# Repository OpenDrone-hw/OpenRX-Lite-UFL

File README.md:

# OpenRX Lite-UFL

Open-source 2.4 GHz ExpressLRS radio control receiver module with telemetry,
for any radio-controlled build: cars, boats, robots and aircraft. OpenRX Lite-UFL
combines an ESP32-C3 and SX1281 with a U.FL link-antenna connector in a
10.0 x 11.5 mm board.
It passes the received channels over serial (CRSF) on its RX and TX pads to a
controller, for example a flight controller or a vehicle or robot controller.

## Specifications

| | |
|---|---|
| Band | 2.4 GHz |
| Radio | SX1281 |
| Antenna | U.FL |
| Telemetry power | 13 dBm (20 mW) |
| Protocol | CRSF |
| MCU | ESP32-C3 |
| Input | 5 V pad |
| Firmware | ExpressLRS |
| Flashing | Betaflight passthrough or Wi-Fi |
| Dimensions | 10.0 x 11.5 mm |
| PCB | 6-layer, 1.0 mm |

Technical write-up, part list and layout constraints: [AGENTS.md](AGENTS.md).

## In the line

What pairs with what, and what is available:
[opendrone.be](https://opendrone.be).

## Contributing

See [CONTRIBUTING.md](CONTRIBUTING.md).

## License

Hardware licensed under [CERN-OHL-S-2.0](https://ohwr.org/cern_ohl_s_v2.txt),
see [LICENSE](LICENSE).

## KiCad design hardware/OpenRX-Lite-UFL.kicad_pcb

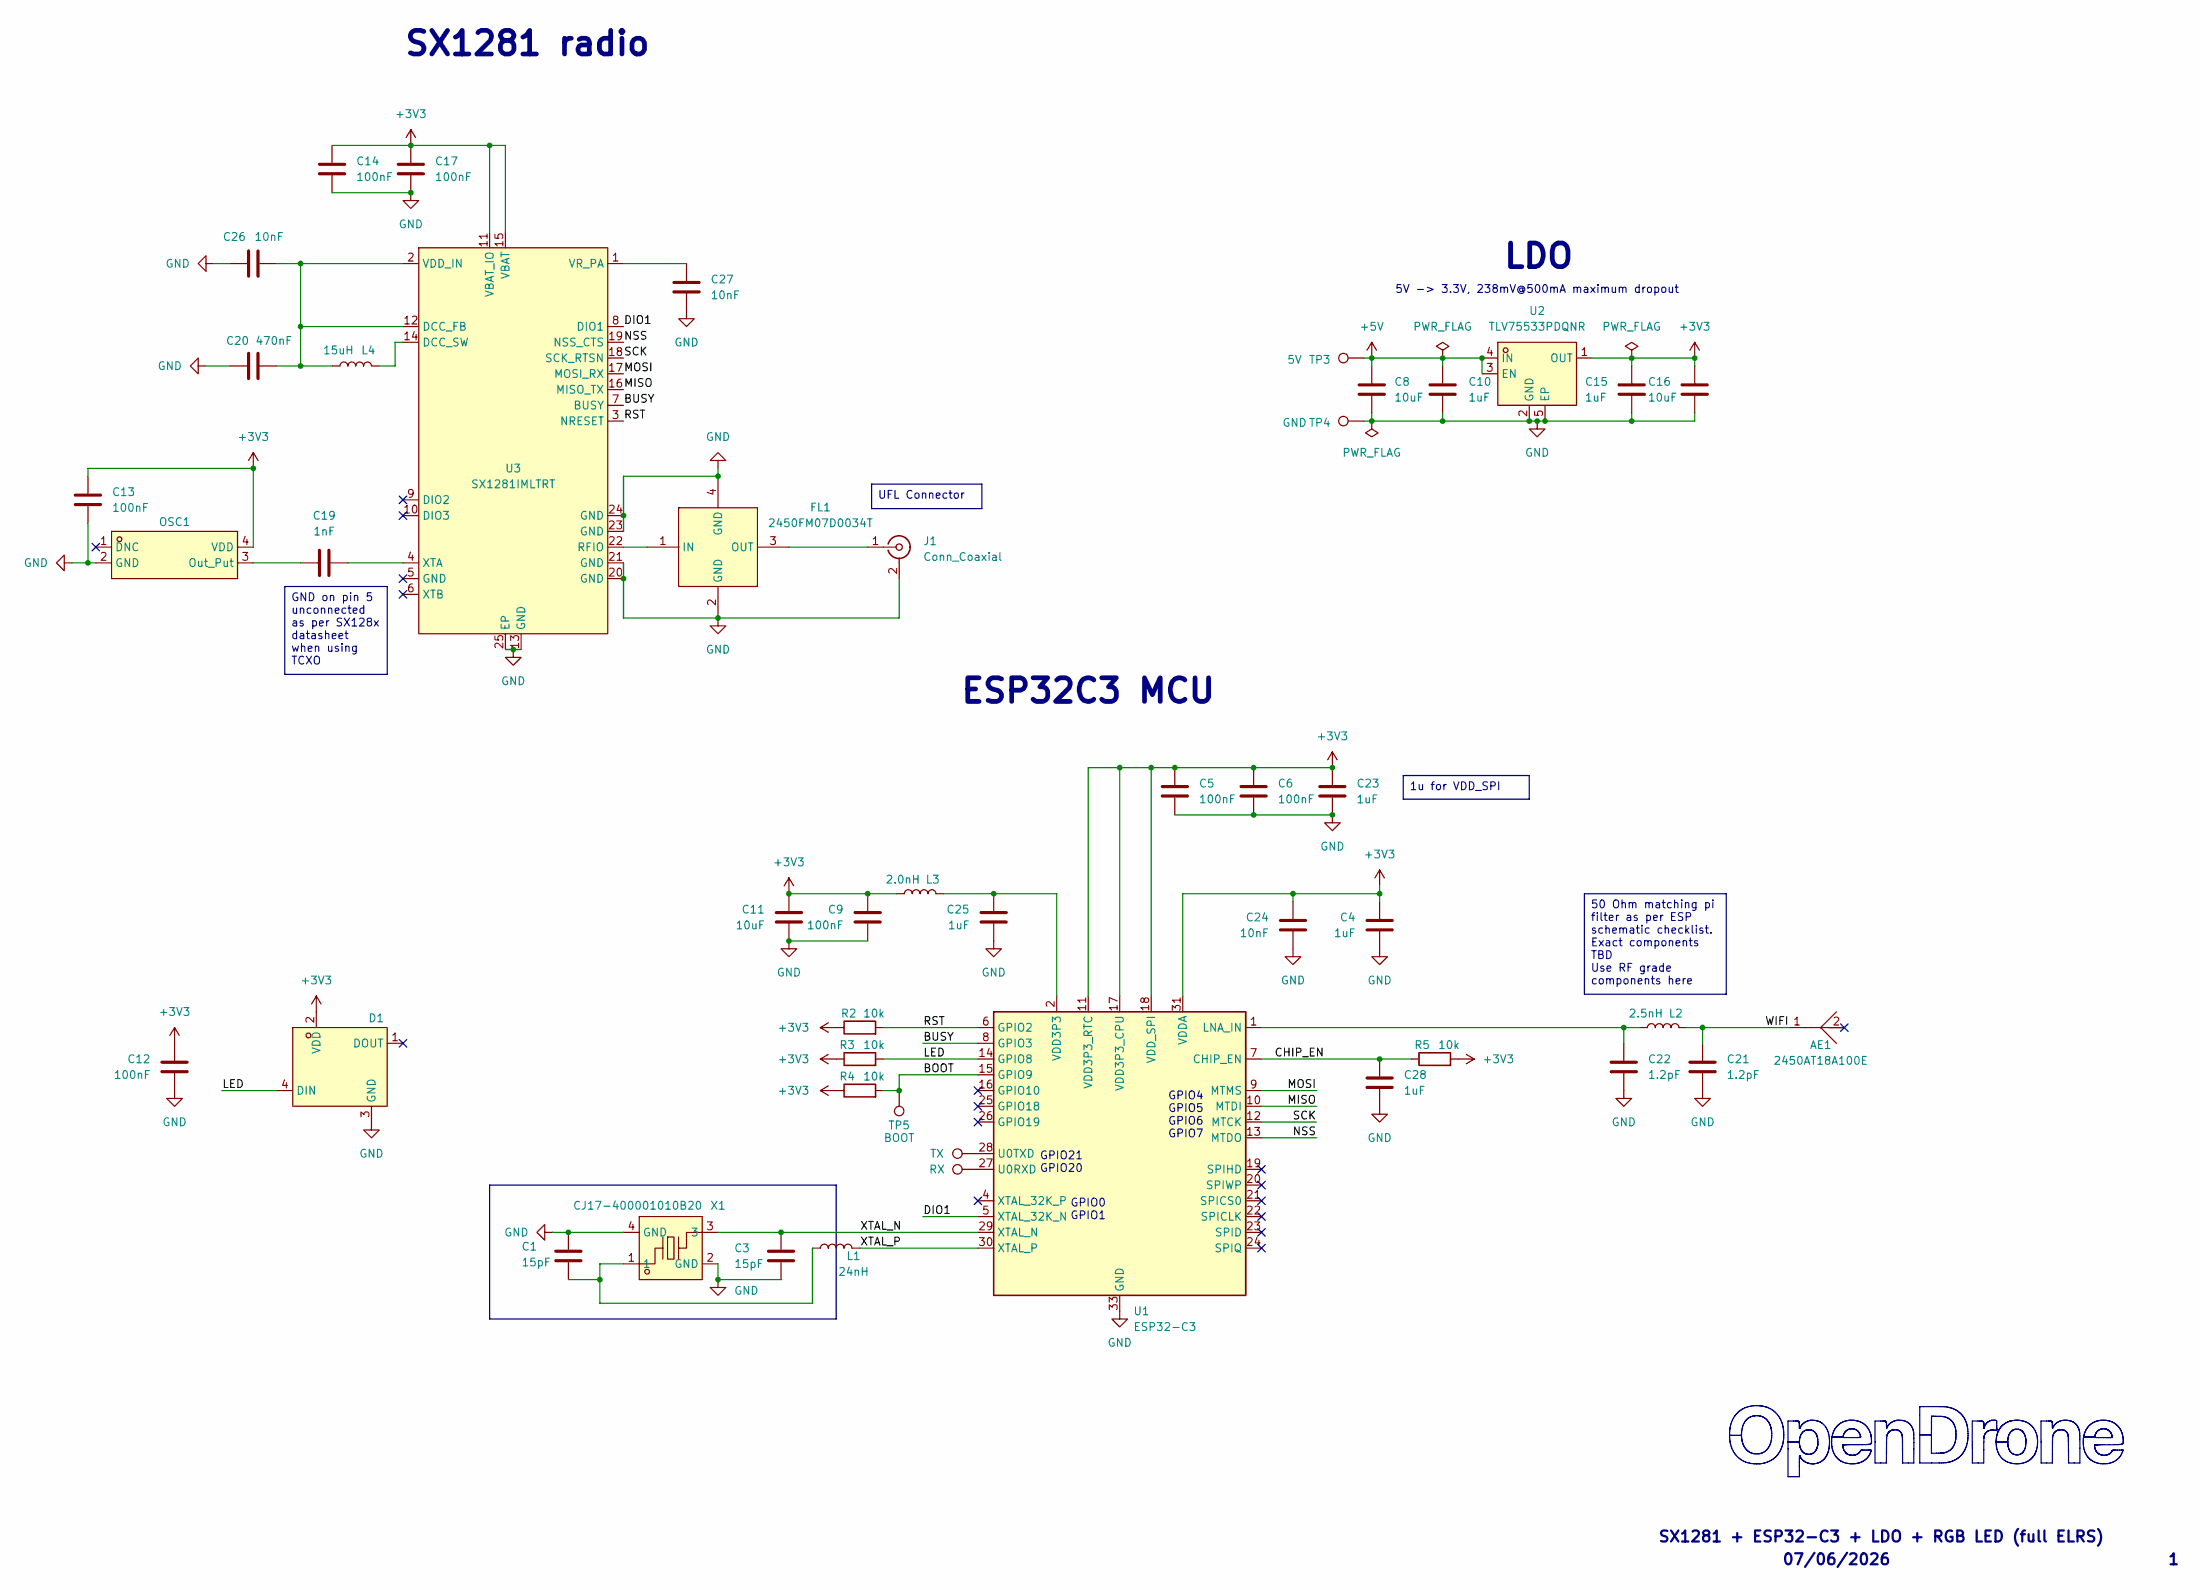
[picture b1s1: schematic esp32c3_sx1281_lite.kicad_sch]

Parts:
AE1: 2450AT18A100E; ANT-SMD_L3.2-W1.6; MPN 2450AT18A100E; LCSC Part C89334
C1, C3: 15pF; C_0201_0603Metric; MPN GRM0335C1H150JA01D; LCSC C85891
C4, C10, C15, C23, C25, C28: 1uF; C_0201_0603Metric; MPN GRM033R61A105ME44D; LCSC C76935
C5, C6, C9, C12, C13, C14, C17: 100nF; C_0201_0603Metric; MPN GRM033R61E104KE14D; LCSC C76939
C8, C16: 10uF; C_0402_1005Metric; MPN CL05A106MQ5NUNC; LCSC C15525
C11: 10uF; C_0402_1005Metric; MPN GRM155R60J106ME44D; LCSC C76991
C19: 1nF; C_0201_0603Metric; MPN 0201B102K500NT; LCSC C66942
C20: 470nF; C_0201_0603Metric; MPN GRM033R60J474KE90D; LCSC C85926
C21, C22: 1.2pF; C_0201_0603Metric; MPN GRM0335C1H1R2BA01D; LCSC C85895
C24, C26, C27: 10nF; C_0201_0603Metric; MPN GRM033R61A103KA01J; LCSC C2168164
D1: XL-1010RGBC-WS2812B; LED-SMD_4P-L1.0-W1.0-TL_XL-1010RGBC-WS2812B; MPN XL-1010RGBC-2812B; LCSC C5349953
FL1: 2450FM07D0034T; FILTER-SMD_4P-L1.0-W0.5-L; MPN 2450FM07D0034T; LCSC Part_1 C2651081
J1: Conn_Coaxial; U.FL_Hirose_U.FL-R-SMT-1_Vertical; MPN U.FL-R-SMT-1(80); LCSC C88374
L1: 24nH; L_0201_0603Metric; MPN LQP03TN24NH02D; LCSC C206441
L2: 2.5nH; L_0201_0603Metric; MPN LQP03TN2N5C02D; LCSC C206435
L3: 2.0nH; L_0201_0603Metric; MPN LQP03TN2N0B02D; LCSC C86125
L4: 15uH; L_0805_2012Metric; MPN MLZ2012M150WT000; LCSC C383402
OSC1: OW7EL89CENUNFAYLC-52M; OSC-SMD_4P-L2.0-W1.6-BL_TXC_7Z; MPN OW7EL89CENUNFAYLC-52M; LCSC Part C22434896
R2, R3, R4, R5: 10k; R_0201_0603Metric; MPN RC0201FR-0710KL; LCSC C106225
TP1: RX; SolderPad_1.2x2.0mm
TP2: TX; SolderPad_1.2x2.0mm
TP3: 5V; SolderPad_1.2x2.0mm
TP4: GND; SolderPad_1.2x2.0mm
TP5: BOOT; SolderPad_1.2x2.0mm
U1: ESP32-C3; QFN-32-1EP_5x5mm_P0.5mm_EP3.7x3.7mm; MPN ESP32-C3FH4; LCSC C2858491
U2: TLV75533PDQNR; X2SON-4_L1.0-W1.0-P0.65-TL-EP; MPN TLV75533PDQNR; LCSC Part C2861882
U3: SX1281IMLTRT; QFN-24_L4.0-W4.0-P0.50-TL-EP2.6; MPN SX1281IMLTRT; LCSC Part C2151551
X1: CJ17-400001010B20; CRYSTAL-SMD_4P-L1.6-W1.2-BL; MPN CJ17-400001010B20; LCSC Part C2875272

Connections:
+3V3: C4.1, C5.1, C6.1, C9.1, C11.1, C12.1, C13.1, C14.1, C15.1, C16.1, C17.1, C23.1, C24.1, D1.2 (VDD), L3.2, OSC1.4 (VDD), R2.1, R3.1, R4.1, R5.2, U1.11 (VDD3P3_RTC), U1.17 (VDD3P3_CPU), U1.18 (VDD_SPI), U1.31 (VDDA), U1.32 (VDDA), U2.1 (OUT), U3.11 (VBAT_IO), U3.15 (VBAT)
+5V: C8.1, C10.1, TP3.1 (1_1), U2.3 (EN), U2.4 (IN)
/ESP32-C3 + SX1281 Core (UFL)/BOOT: R4.2, TP5.1 (1_1), U1.15 (GPIO9)
/ESP32-C3 + SX1281 Core (UFL)/BUSY: U1.8 (GPIO3), U3.7 (BUSY)
/ESP32-C3 + SX1281 Core (UFL)/CHIP_EN: C28.1, R5.1, U1.7 (CHIP_EN)
/ESP32-C3 + SX1281 Core (UFL)/DIO1: U1.5 (XTAL_32K_N), U3.8 (DIO1)
/ESP32-C3 + SX1281 Core (UFL)/LED: D1.4 (DIN), R3.2, U1.14 (GPIO8)
/ESP32-C3 + SX1281 Core (UFL)/MISO: U1.10 (MTDI), U3.16 (MISO_TX)
/ESP32-C3 + SX1281 Core (UFL)/MOSI: U1.9 (MTMS), U3.17 (MOSI_RX)
/ESP32-C3 + SX1281 Core (UFL)/NSS: U1.13 (MTDO), U3.19 (NSS_CTS)
/ESP32-C3 + SX1281 Core (UFL)/RST: R2.2, U1.6 (GPIO2), U3.3 (NRESET)
/ESP32-C3 + SX1281 Core (UFL)/SCK: U1.12 (MTCK), U3.18 (SCK_RTSN)
/ESP32-C3 + SX1281 Core (UFL)/WIFI: AE1.1, C21.1, L2.1
/ESP32-C3 + SX1281 Core (UFL)/XTAL_N: C3.1, U1.29 (XTAL_N), X1.3
/ESP32-C3 + SX1281 Core (UFL)/XTAL_P: L1.2, U1.30 (XTAL_P)
GND: C1.2, C3.2, C4.2, C5.2, C6.2, C8.2, C9.2, C10.2, C11.2, C12.2, C13.2, C14.2, C15.2, C16.2, C17.2, C20.1, C21.2, C22.2, C23.2, C24.2, C25.2, C26.1, C27.2, C28.2, D1.3 (GND), FL1.2 (GND), FL1.4 (GND), J1.2 (Ext), OSC1.2 (GND), TP4.1 (1_1), U1.33 (GND), U2.2 (GND), U2.5 (EP), U3.13 (GND), U3.20 (GND), U3.21 (GND), U3.23 (GND), U3.24 (GND), U3.25 (EP), X1.2 (GND), X1.4 (GND)
unnamed: C1.1, L1.1, X1.1
unnamed: C25.1, L3.1, U1.2 (VDD3P3), U1.3 (VDD3P3)
unnamed: FL1.1 (IN), U3.22 (RFIO)
unnamed: FL1.3 (OUT), J1.1 (In)
unnamed: C19.1, OSC1.3 (Out_Put)
unnamed: C22.1, L2.2, U1.1 (LNA_IN)
unnamed: TP1.1 (1_1), U1.27 (U0RXD)
unnamed: TP2.1 (1_1), U1.28 (U0TXD)
unnamed: C20.2, C26.2, L4.1, U3.2 (VDD_IN), U3.12 (DCC_FB)
unnamed: L4.2, U3.14 (DCC_SW)
unnamed: C27.1, U3.1 (VR_PA)
unnamed: C19.2, U3.4 (XTA)

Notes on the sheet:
5V -> 3.3V, 238mV@500mA maximum dropout
GPIO0 GPIO1
GPIO21 GPIO20
SX1281 + ESP32-C3 + LDO + RGB LED (full ELRS)
GPIO4 GPIO5 GPIO6 GPIO7
SX1281 radio
LDO
ESP32C3 MCU
07/06/2026
GND on pin 5 unconnected as per SX128x datasheet when using TCXO
UFL Connector
1u for VDD_SPI
50 Ohm matching pi filter as per ESP schematic checklist. Exact components TBD Use RF grade components here

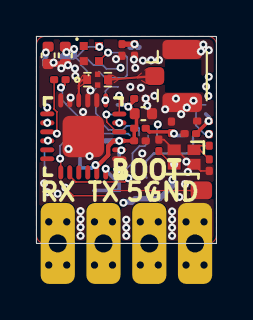
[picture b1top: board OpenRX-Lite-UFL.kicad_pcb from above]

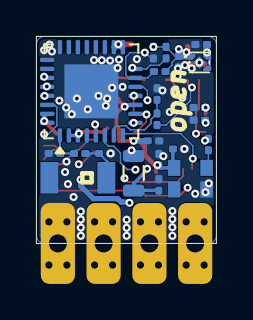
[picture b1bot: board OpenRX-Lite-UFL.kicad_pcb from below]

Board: 6 copper layers, 10.0 x 11.5 mm, 47 parts (22 on the bottom side), 28 nets.

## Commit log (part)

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2026-03-23 Fix Gemini crystal load caps to 18pF (C62164), matching Lite and Mono
2026-03-23 Repo cleanup: remove ERC reports, lock files, backup dirs, fix gitignore
2026-03-23 Add SolderPad_1.2x2.0mm with 25% rounded corners, 2.0mm pitch standard
2026-03-23 Import SKY13588-460LF SP3T RF switch (C2151906) into shared library
2026-03-23 Final topology: Mono + Gemini netlist with SKY13588 RF switch
    - SKY13588-460LF imported into shared library
    - Complete netlist for Mono (1×LR1121 + SKY13588 + Johanson IPD + DEA LPF → 1 UFL)
    - Gemini = 2× Mono RF chains + ESP32-C3 True Diversity GPIO mapping
    - GPIO maps match official ELRS Generic C3 LR1121 and True Diversity targets
    - Routing notes for RF paths included
    - Mono needs complete GPIO rewire to match ELRS target
2026-03-23 FINAL_NETLIST v3: SKY13588 as band combiner, RFX2401C kept for 100mW
    Based on RadioMaster XR4 teardown analysis:
    - SKY13588 serves as both sub-GHz path switch AND band combiner
    - Johanson IPD in direct-tie mode (RX/TX_LP/TX_HP joined) → SKY13588 J1
    - 2.4GHz: RFIO_HF → DEA LPF → RFX2401C → SKY13588 J2
    - SKY13588 RFC → DC block → UFL → dual-band antenna
    - RFX2401C kept for 100mW market parity
2026-03-24 Repo cleanup: final state for handoff
    - Clean README with architecture, BOM, CE notes, status
    - Remove dated analysis files (absorbed into FINAL_NETLIST + KICAD_WORKFLOW)
    - Remove stale OpenRX-Dual (archived), ERC reports, backups, prl files
    - Updated .gitignore for .kicad_dru, production backups
    - CERN-OHL-S v2 license confirmed
    - 3 active projects: Lite, Mono, Gemini
2026-03-24 Revise target prices in receiver specifications
    Updated target prices for Lite, Mono, and Gemini models.
2026-03-24 Consolidate active RX docs and shared project metadata
2026-04-21 initial routing for all
2026-04-27 final route
2026-04-28 Set via netclass + dimension defaults to 0.3/0.2mm on all 4 boards
2026-04-28 switch to 0.2mm vias
2026-04-28 gitignore JLC per-quote BOM markdown drops
2026-05-08 OpenRX Lite (UFL + molex)
2026-05-13 fab and placement output for combined order
2026-06-07 annotate
